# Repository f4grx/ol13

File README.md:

# ol13
1888 local oscillator, made after DF6NP design.

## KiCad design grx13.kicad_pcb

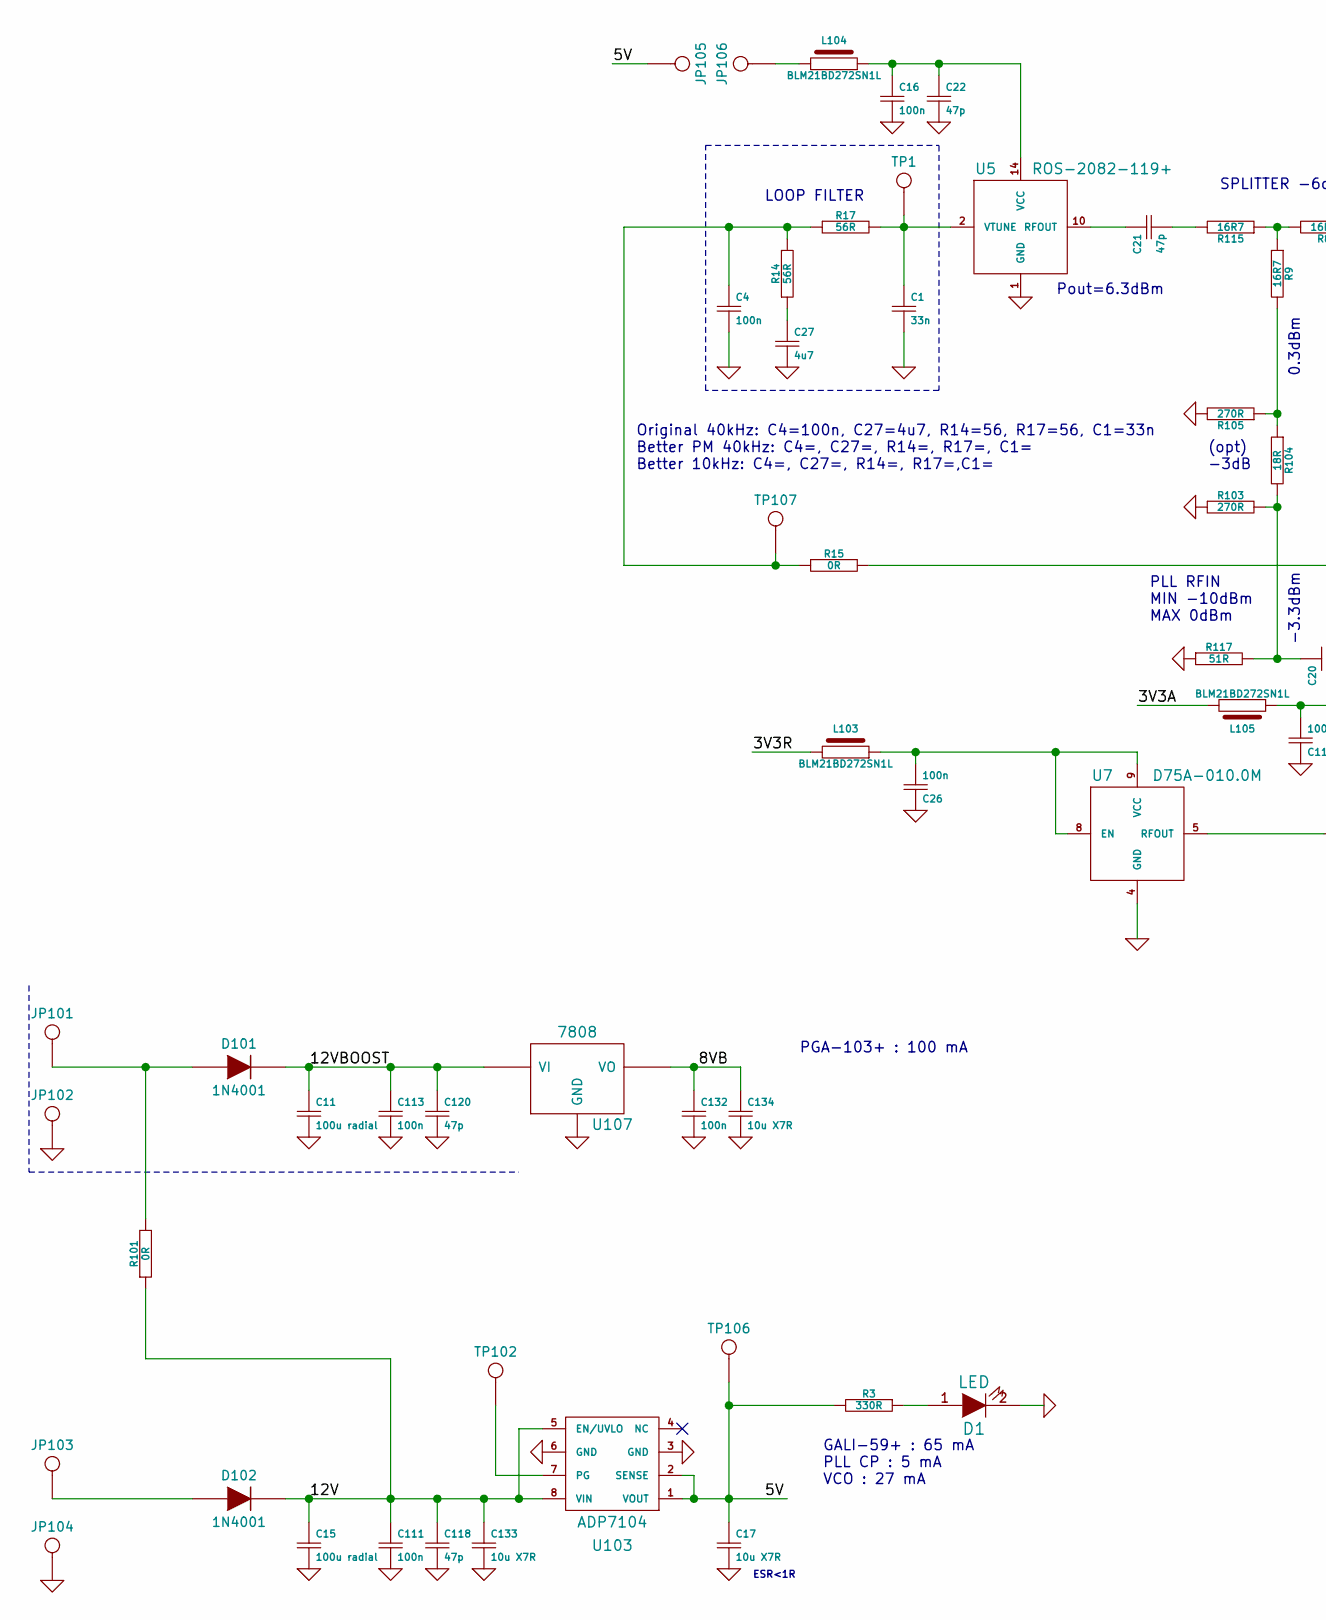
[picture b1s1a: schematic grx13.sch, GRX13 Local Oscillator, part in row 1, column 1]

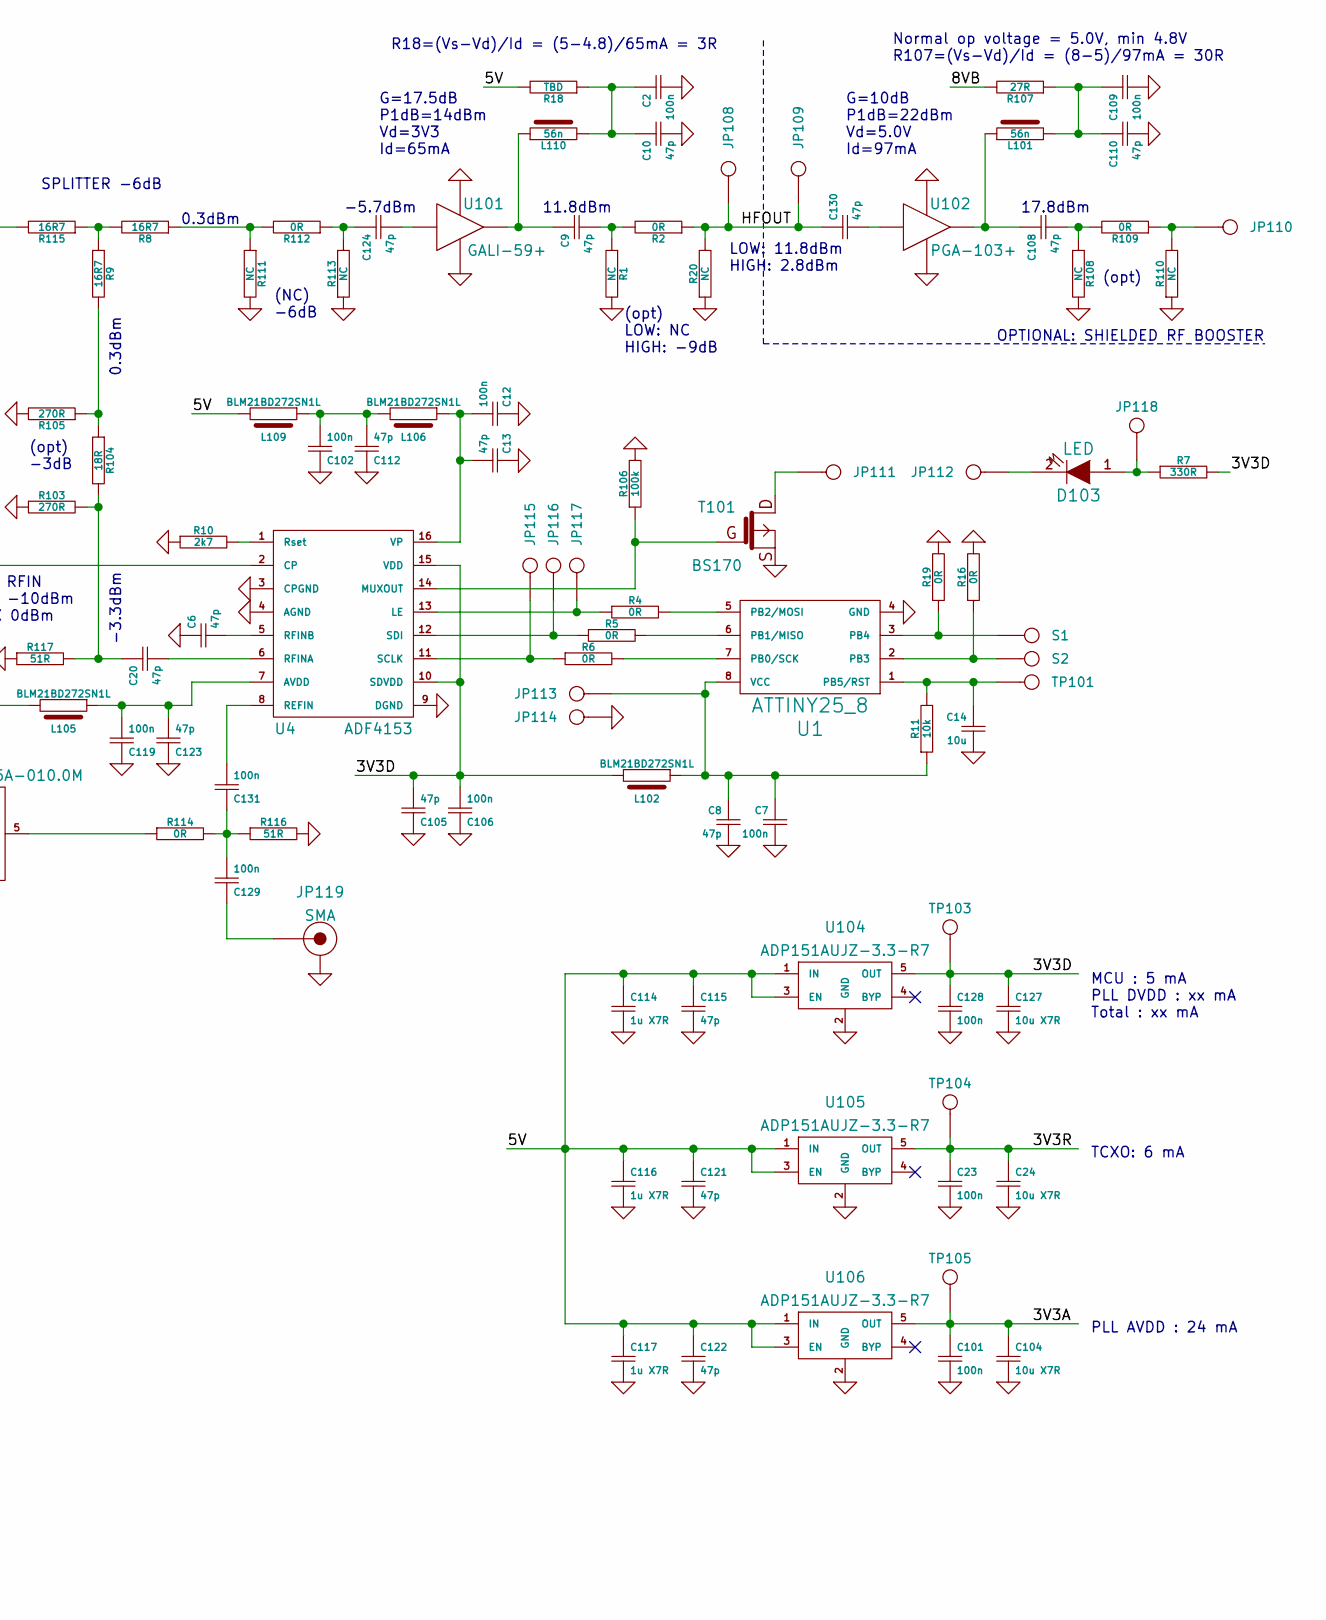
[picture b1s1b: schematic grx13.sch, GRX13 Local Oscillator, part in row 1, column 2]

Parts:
C1: 33n; 0805
C2, C7, C12, C16, C23, C26, C101, C102, C106, C109, C111, C113, C119, C128, C129, C131, C132: 100n; 0805; PartNo 08055C104KAT2A; Farnell 499687
C4: 100n; 0805
C6, C8, C9, C10, C13, C20, C21, C22, C105, C108, C110, C112, C115, C118, C120, C121, C122, C123, C124, C130: 47p; 0805; PartNo 08051A470JAT2A; Farnell 499160
C11, C15: 100u radial; C2V8
C14: 10u; 1206
C17, C24, C104, C127, C133: 10u X7R; 1206; PartNo 1206YC106KAT2A; Farnell 1657943
C27: 4u7; 1206
C114: 1u X7R; 0805; PartNo C2012X7S2A105K125AB
C116, C117: 1u X7R; 0805
C134: 10u X7R; 1206; PartNo 1206YC106KAT2A
D1, D103: LED; 0805
D101, D102: 1N4001; D4
JP101: CONN_1; HOLE_PTH_R_08_16; PartNo nobom; Farnell F
JP102, JP103, JP104, JP105, JP106, JP111, JP112, JP113, JP114, JP115, JP116, JP117, JP118: CONN_1; HOLE_PTH_R_08_16; PartNo nobom
JP108, JP109, JP110: CONN_1; HOLE_SMD_S_15; PartNo nobom
JP119: SMA; SMA_TH; PartNo nobom
L101, L110: 56n; 0805
L102, L103, L104, L105, L106, L109: BLM21BD272SN1L; 0805; PartNo BLM21BD272SN1L; Farnell 1515647
R1, R20, R108, R110, R111, R113: NC; 0805
R2, R4, R5, R6, R15, R16, R19, R101, R109, R112, R114: 0R; 0805
R3, R7: 330R; 0805
R8, R9, R115: 16R7; 0805
R10: 2k7; 0805
R11: 10k; 0805
R14, R17: 56R; 0805
R18: TBD; 1206
R103, R105: 270R; 0805
R104: 18R; 0805
R106: 100k; 0805
R107: 27R; 1206
R116, R117: 51R; 0805
S1, S2: CONN_1; HOLE_PTH_R_08_16; PartNo nobom
T101: BS170; SOT23GDS; PartNo BS170FTA; Farnell 9526005
TP1, TP101, TP102, TP103, TP104, TP105, TP106, TP107: CONN_1; HOLE_PTH_R_06_12; PartNo nobom
U1: ATTINY25_8; SO8N; PartNo ATTINY25V-10SSU
U4: ADF4153; TSSOP16; PartNo ADF4153ABRUZ; Mouser 584-ADF4153ABRUZ
U5: ROS-2082-119+; CK605; PartNo ROS-2082-119+; Farnell NA
U7: D75A-010.0M; D75A; PartNo D75A-010.0M; Farnell NA
U101: GALI-59+; SOT89; PartNo GALI-59+; Farnell NA
U102: PGA-103+; SOT89; PartNo PGA-103+; Farnell NA
U103: ADP7104; SO8N; PartNo ADP7104ARDZ-5.0-R7; Farnell NA
U104, U105, U106: ADP151AUJZ-3.3-R7; SOT23-5; PartNo ADP151AUJZ-3.3-R7; Mouser 584-ADP151AUJZ-3.3R7
U107: 7808; DPAK2; PartNo MC7808CDTT5G; Farnell 1652338

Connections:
/3V3A: C101.1, C104.1, L105.2 (OUT), TP105.1, U106.5 (OUT)
/3V3D: C105.2, C106.2, C127.1, C128.1, L102.2 (OUT), R7.2 (OUT), TP103.1, U4.10 (SDVDD), U4.15 (VDD), U104.5 (OUT)
/3V3R: C23.1, C24.1, L103.2 (OUT), TP104.1, U105.5 (OUT)
/5V: C17.1, C114.1, C115.1, C116.1, C117.1, C121.1, C122.1, JP105.1, L109.2 (OUT), R3.2 (OUT), R18.2 (OUT), TP106.1, U103.1 (VOUT), U103.2 (SENSE), U104.1 (IN), U104.3 (EN), U105.1 (IN), U105.3 (EN), U106.1 (IN), U106.3 (EN)
/8VB: C132.1, C134.1, R107.2 (OUT), U107.3 (VO)
/12V: C15.1, C111.1, C118.1, C133.1, D102.2 (K), R101.1 (IN), U103.5 (EN/UVLO), U103.8 (VIN)
/12VBOOST: C11.1, C113.1, C120.1, D101.2 (K), U107.1 (VI)
/HFOUT: C130.1, JP108.1, JP109.1, R2.1 (IN), R20.2 (OUT)
GND: C1.2, C2.2, C4.2, C6.1, C7.2, C8.2, C10.2, C11.2, C12.1, C13.1, C14.2, C15.2, C16.2, C17.2, C22.2, C23.2, C24.2, C26.1, C27.2, C101.2, C102.1, C104.2, C105.1, C106.1, C109.2, C110.2, C111.2, C112.1, C113.2, C114.2, C115.2, C116.2, C117.2, C118.2, C119.1, C120.2, C121.2, C122.2, C123.1, C127.2, C128.2, C132.2, C133.2, C134.2, D1.2 (K), JP102.1, JP104.1, JP114.1, JP119.2, R1.2 (OUT), R10.1 (IN), R16.2 (OUT), R19.2 (OUT), R20.1 (IN), R103.1 (IN), R105.2 (OUT), R106.2 (OUT), R108.2 (OUT), R110.1 (IN), R111.2 (OUT), R113.1 (IN), R116.2 (OUT), R117.1 (IN), T101.S, U1.4 (GND), U4.3 (CPGND), U4.4 (AGND), U4.9 (DGND), U5.1 (GND), U7.4 (GND), U101.2 (GND), U102.2 (GND), U103.3 (GND), U103.6 (GND), U104.2 (GND), U105.2 (GND), U106.2 (GND), U107.2 (GND)
unnamed: C1.1, R17.2 (OUT), TP1.1, U5.2 (VTUNE)
unnamed: C4.1, R14.2 (OUT), R15.1 (IN), R17.1 (IN), TP107.1
unnamed: C6.2, U4.5 (RFINB)
unnamed: C7.1, C8.1, JP113.1, L102.1 (IN), R11.1 (IN), U1.8 (VCC)
unnamed: C9.1, L110.1 (IN), U101.3 (OUT)
unnamed: C9.2, R1.1 (IN), R2.2 (OUT)
unnamed: C2.1, C10.1, L110.2 (OUT), R18.1 (IN)
unnamed: C12.2, C13.2, L106.1 (IN), U4.16 (VP)
unnamed: C14.1, R11.2 (OUT), TP101.1, U1.1 (PB5/RST)
unnamed: C16.1, C22.1, L104.1 (IN), U5.14 (VCC)
unnamed: C20.1, R103.2 (OUT), R104.2 (OUT), R117.2 (OUT)
unnamed: C20.2, U4.6 (RFINA)
unnamed: C21.1, U5.10 (RFOUT)
unnamed: C21.2, R115.2 (OUT)
unnamed: C26.2, L103.1 (IN), U7.8 (EN), U7.9 (VCC)
unnamed: C27.1, R14.1 (IN)
unnamed: C102.2, C112.2, L106.2 (OUT), L109.1 (IN)
unnamed: C108.1, L101.1 (IN), U102.3 (OUT)
unnamed: C108.2, R108.1 (IN), R109.2 (OUT)
unnamed: C109.1, C110.1, L101.2 (OUT), R107.1 (IN)
unnamed: C119.2, C123.2, L105.1 (IN), U4.7 (AVDD)
unnamed: C124.1, R112.1 (IN), R113.2 (OUT)
unnamed: C124.2, U101.1 (IN)
unnamed: C129.1, JP119.1
unnamed: C129.2, C131.1, R114.2 (OUT), R116.1 (IN)
unnamed: C130.2, U102.1 (IN)
unnamed: C131.2, U4.8 (REFIN)
unnamed: D1.1 (A), R3.1 (IN)
unnamed: D101.1 (A), JP101.1, R101.2 (OUT)
unnamed: D102.1 (A), JP103.1
unnamed: D103.1 (A), JP118.1, R7.1 (IN)
unnamed: D103.2 (K), JP112.1
unnamed: JP106.1, L104.2 (OUT)
unnamed: JP110.1, R109.1 (IN), R110.2 (OUT)
unnamed: JP111.1, T101.D
unnamed: JP115.1, R6.1 (IN), U4.11 (SCLK)
unnamed: JP116.1, R5.1 (IN), U4.12 (SDI)
unnamed: JP117.1, R4.1 (IN), U4.13 (LE)
unnamed: R4.2 (OUT), U1.5 (PB2/MOSI)
unnamed: R5.2 (OUT), U1.6 (PB1/MISO)
unnamed: R6.2 (OUT), U1.7 (PB0/SCK)
unnamed: R10.2 (OUT), U4.1 (Rset)
unnamed: R15.2 (OUT), U4.2 (CP)
unnamed: R16.1 (IN), S2.1, U1.2 (PB3)
unnamed: R19.1 (IN), S1.1, U1.3 (PB4)
unnamed: R9.2 (OUT), R104.1 (IN), R105.1 (IN)
unnamed: R106.1 (IN), T101.G, U4.14 (MUXOUT)
unnamed: R8.1 (IN), R111.1 (IN), R112.2 (OUT)
unnamed: R114.1 (IN), U7.5 (RFOUT)
unnamed: R8.2 (OUT), R9.1 (IN), R115.1 (IN)
unnamed: TP102.1, U103.7 (PG)

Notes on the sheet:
OPTIONAL: SHIELDED RF BOOSTER
(opt) -3dB
(NC) -6dB
(opt) LOW: NC HIGH: -9dB
LOOP FILTER
Pout=6.3dBm
SPLITTER -6dB
G=10dB P1dB=22dBm Vd=5.0V Id=97mA
G=17.5dB P1dB=14dBm Vd=3V3 Id=65mA
0.3dBm
PLL RFIN MIN -10dBm MAX 0dBm
-3.3dBm
-5.7dBm
11.8dBm
LOW: 11.8dBm HIGH: 2.8dBm
17.8dBm
(opt)
R18=(Vs-Vd)/Id = (5-4.8)/65mA = 3R
Normal op voltage = 5.0V, min 4.8V R107=(Vs-Vd)/Id = (8-5)/97mA = 30R
MCU : 5 mA PLL DVDD : xx mA Total : xx mA
TCXO: 6 mA
PLL AVDD : 24 mA
PGA-103+ : 100 mA
GALI-59+ : 65 mA PLL CP : 5 mA VCO : 27 mA
ESR<1R
Original 40kHz: C4=100n, C27=4u7, R14=56, R17=56, C1=33n Better PM 40kHz: C4=, C27=, R14=, R17=, C1= Better 10kHz: C4=, C27=, R14=, R17=,C1=

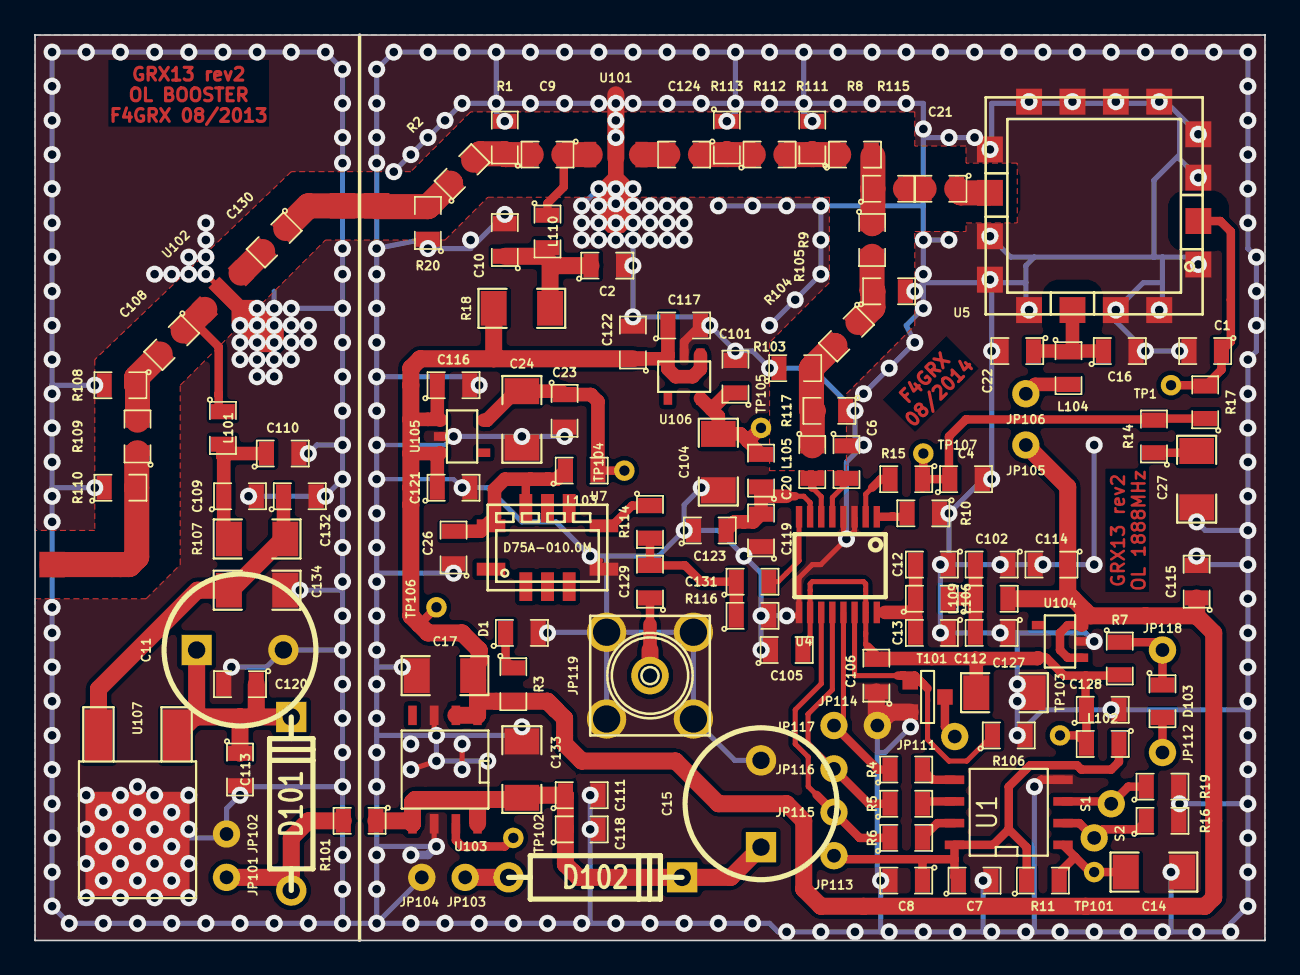
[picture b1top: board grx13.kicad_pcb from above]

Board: 2 copper layers, 72.0 x 53.0 mm, 138 parts (0 on the bottom side), 60 nets.

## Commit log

2018-02-24 ol13 as fabricated
2018-02-24 add a pdf
